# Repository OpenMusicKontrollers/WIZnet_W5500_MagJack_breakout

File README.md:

# WIZnet W5500 MagJack breakout 

## About
This is the PCB design of a breakout board for [WIZnet](http://www.wiznet.co.kr)'s 
[W5500](http://wizwiki.net/wiki/doku.php?id=products:w5500:start) hardwired TCP/IP chip with a MagJack for DIY production.

## Prerequisites
To be used with [KiCAD](http://www.kicad-pcb.org).

## License
This is open source hardware and licensed under [CERN OHL v.1.2](http://ohwr.org/cernohl).

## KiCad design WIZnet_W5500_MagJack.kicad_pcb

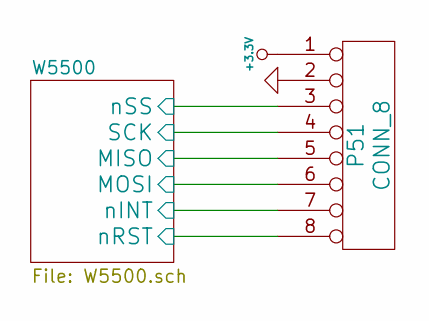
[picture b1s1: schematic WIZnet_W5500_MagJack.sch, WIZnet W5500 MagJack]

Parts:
P51: CONN_8

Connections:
+3.3V: P51.1; also elsewhere on the board
/W5500/MISO: P51.5; also elsewhere on the board
/W5500/MOSI: P51.6; also elsewhere on the board
/W5500/SCK: P51.4; also elsewhere on the board
/W5500/nINT: P51.7; also elsewhere on the board
/W5500/nRST: P51.8; also elsewhere on the board
/W5500/nSS: P51.3; also elsewhere on the board
GND: P51.2; also elsewhere on the board

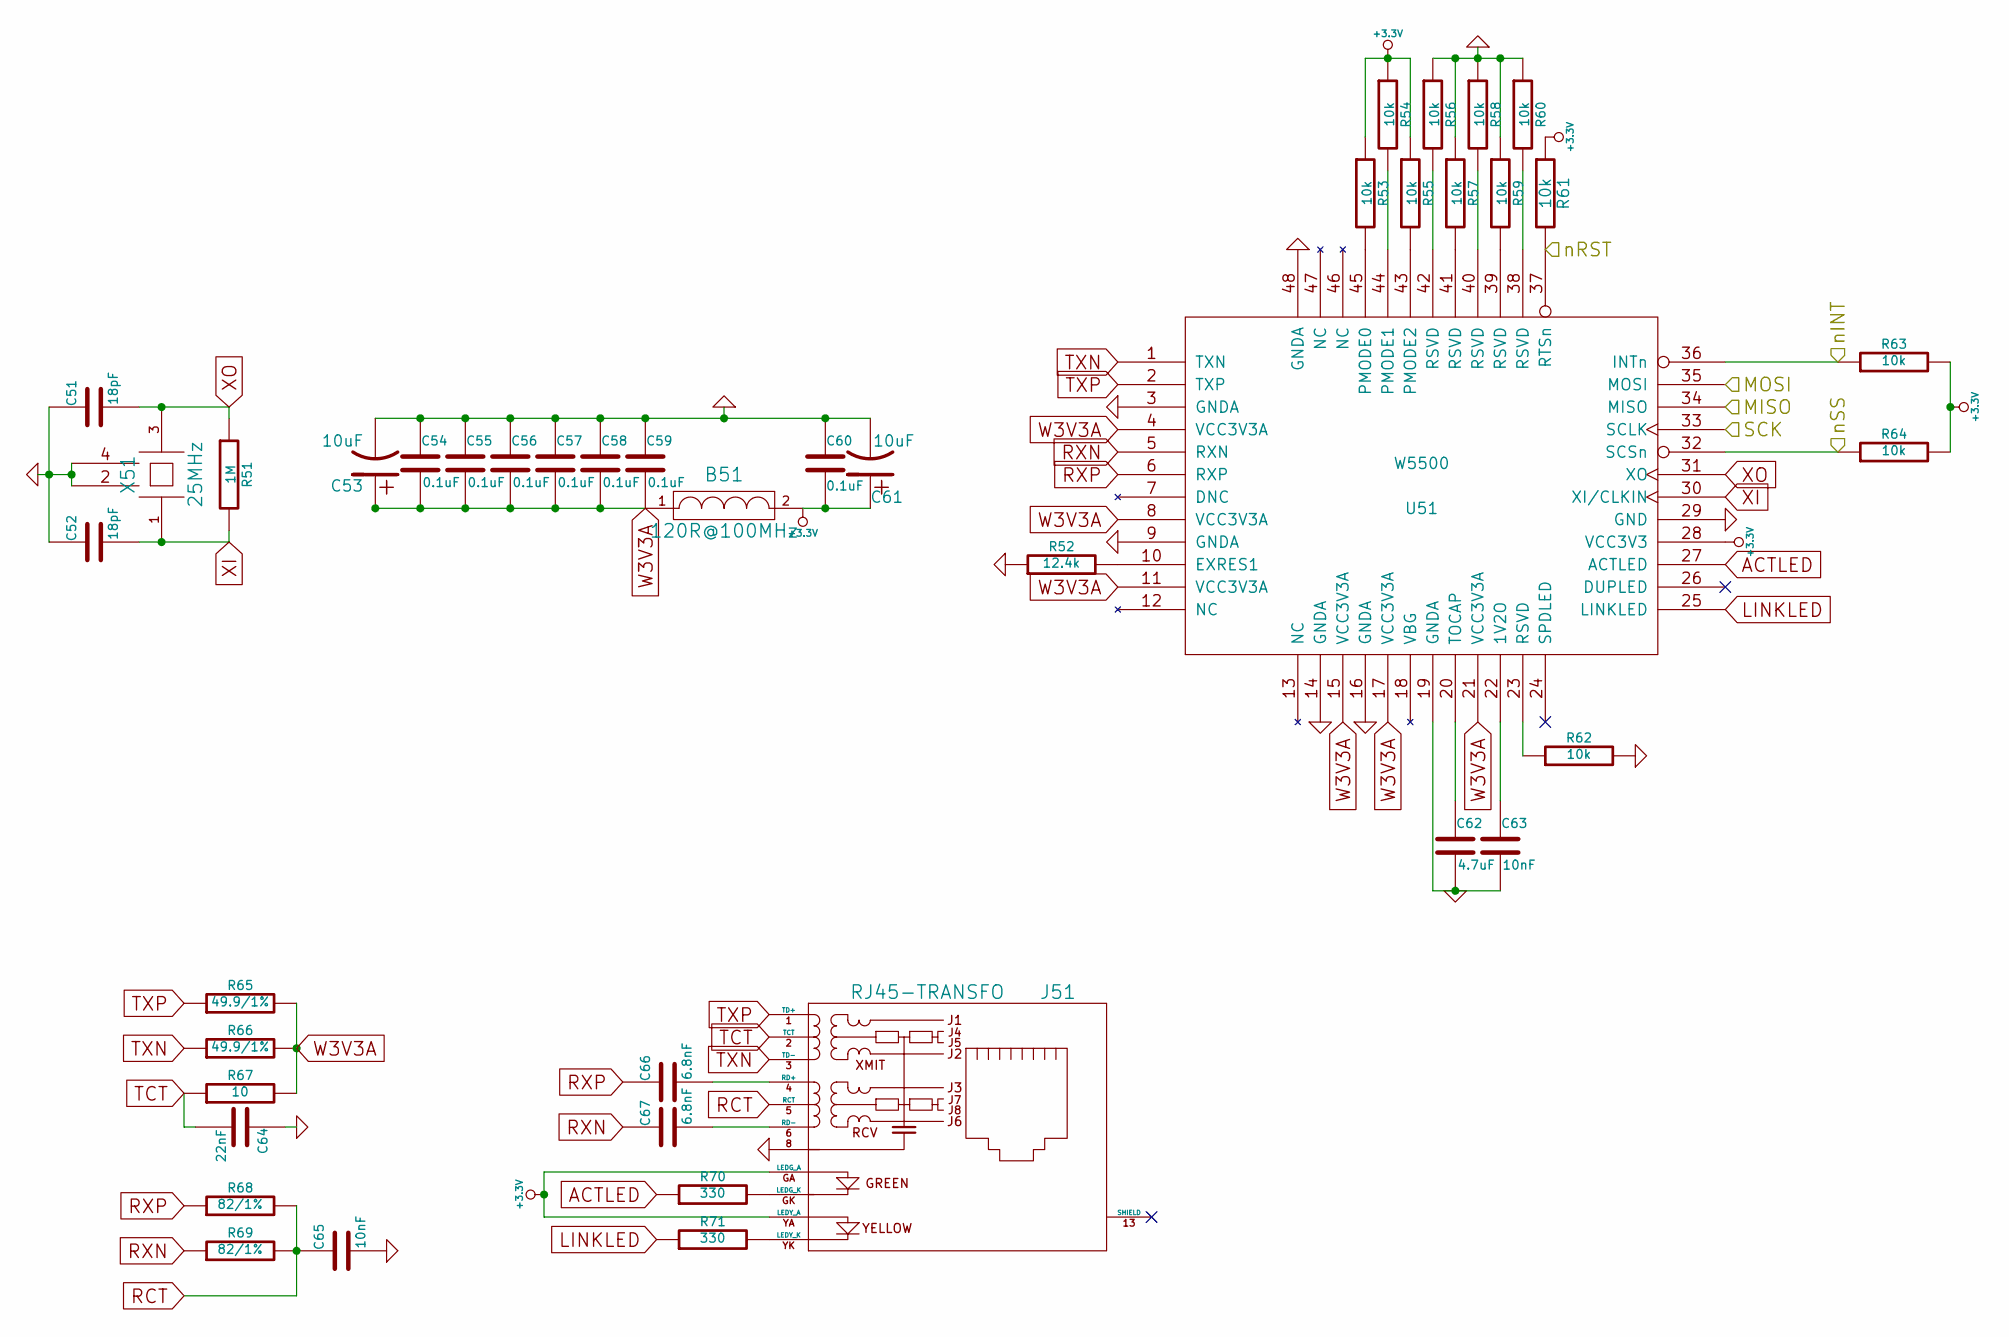
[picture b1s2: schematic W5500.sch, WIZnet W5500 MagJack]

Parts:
B51: 120R@100MHz; Digi-Key 240-2383-1-ND
C51, C52: 18pF; Digi-Key 311-1061-1-ND
C53, C61: 10uF; Digi-Key 478-8456-1-ND
C54, C55, C56, C57, C58, C59, C60: 0.1uF; Digi-Key 445-1314-1-ND
C62: 4.7uF; Digi-Key 445-6859-1-ND
C63, C65: 10nF; Digi-Key 311-1572-1-ND
C64: 22nF; Digi-Key 311-1370-1-ND
C66, C67: 6.8nF; Digi-Key 311-1084-1-ND
J51: RJ45-TRANSFO; Digi-Key 380-1106-ND
R51: 1M; Digi-Key P1.00MHCT-ND
R52: 12.4k; Digi-Key P12.4KHCT-ND
R53, R54, R55, R56, R57, R58, R59, R60, R62, R63, R64: 10k; Digi-Key P10KGCT-ND
R61: 10k; Digi-Key P10KGCT-ND
R65, R66: 49.9/1%; Digi-Key P49.9HCT-ND
R67: 10; Digi-Key P10.0HCT-ND
R68, R69: 82/1%; Digi-Key P82.0HCT-ND
R70, R71: 330; Digi-Key P330HCT-ND
U51: W5500; MODULE; Digi-Key 1278-1021-ND
X51: 25MHz; Digi-Key CTX826CT-ND

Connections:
+3.3V: B51.2, C60.2, C61.1, J51.GA (LEDG_A), J51.YA (LEDY_A), R53.1, R54.1, R55.1, R61.1, R63.2, R64.2, U51.28 (VCC3V3); also elsewhere on the board
/W5500/MISO: U51.34 (MISO); also elsewhere on the board
/W5500/MOSI: U51.35 (MOSI); also elsewhere on the board
/W5500/SCK: U51.33 (SCLK); also elsewhere on the board
/W5500/nINT: R63.1, U51.36 (INTn); also elsewhere on the board
/W5500/nRST: R61.2, U51.37 (RTSn); also elsewhere on the board
/W5500/nSS: R64.1, U51.32 (SCSn); also elsewhere on the board
ACTLED: R70.1, U51.27 (ACTLED)
GND: C51.1, C52.1, C53.2, C54.1, C55.1, C56.1, C57.1, C58.1, C59.1, C60.1, C61.2, C62.2, C63.2, C64.1, C65.2, J51.8, R52.1, R56.1, R57.1, R58.1, R59.1, R60.1, R62.2, U51.3 (GNDA), U51.9 (GNDA), U51.14 (GNDA), U51.16 (GNDA), U51.19 (GNDA), U51.29 (GND), U51.48 (GNDA), X51.2 (GND), X51.4 (GND); also elsewhere on the board
LINKLED: R71.1, U51.25 (LINKLED)
unnamed: R54.2, U51.44 (PMODE1)
unnamed: C63.1, U51.22 (1V2O)
unnamed: C62.1, U51.20 (TOCAP)
unnamed: R59.2, U51.39 (RSVD)
unnamed: R60.2, U51.38 (RSVD)
unnamed: C67.2, J51.6 (RD-)
unnamed: C66.2, J51.4 (RD+)
unnamed: R56.2, U51.42 (RSVD)
unnamed: R62.1, U51.23 (RSVD)
unnamed: R58.2, U51.40 (RSVD)
unnamed: R57.2, U51.41 (RSVD)
unnamed: R52.2, U51.10 (EXRES1)
unnamed: J51.GK (LEDG_K), R70.2
unnamed: R53.2, U51.45 (PMODE0)
unnamed: R55.2, U51.43 (PMODE2)
unnamed: J51.YK (LEDY_K), R71.2
RCT: C65.1, J51.5 (RCT), R68.2, R69.2
RXN: C67.1, R69.1, U51.5 (RXN)
RXP: C66.1, R68.1, U51.6 (RXP)
TCT: C64.2, J51.2 (TCT), R67.1
TXN: J51.3 (TD-), R66.1, U51.1 (TXN)
TXP: J51.1 (TD+), R65.1, U51.2 (TXP)
W3V3A: B51.1, C53.1, C54.2, C55.2, C56.2, C57.2, C58.2, C59.2, R65.2, R66.2, R67.2, U51.4 (VCC3V3A), U51.8 (VCC3V3A), U51.11 (VCC3V3A), U51.15 (VCC3V3A), U51.17 (VCC3V3A), U51.21 (VCC3V3A)
XI: C52.2, R51.2, U51.30 (XI/CLKIN), X51.1
XO: C51.2, R51.1, U51.31 (XO), X51.3

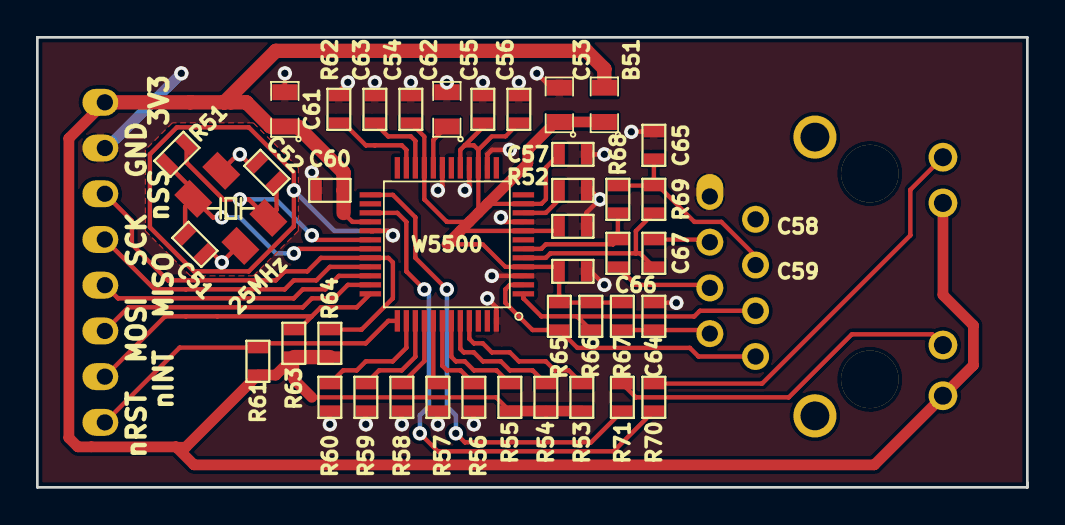
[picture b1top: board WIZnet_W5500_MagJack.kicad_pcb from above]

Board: 2 copper layers, 55.0 x 25.0 mm, 43 parts (0 on the bottom side), 35 nets.

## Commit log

2013-11-25 polished W5500 integration, add AD75019
2014-02-21 small updates to WIYnet W5500 breakout
2014-03-02 solder paste clearence for 125um mylar stencils
2014-03-02 add README.md and licensing
2014-03-02 path fixes after repo split

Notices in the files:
W5500.sch:
Copyright (c) 2014 Hanspeter Portner (dev@open-music-kontrollers.ch)
WIZnet_W5500_MagJack.sch:
Copyright (c) 2013 Hanspeter Portner (dev@open-music-kontrollers.ch)
